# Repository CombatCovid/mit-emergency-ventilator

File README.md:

# MIT Emergency Ventilator (E-Vent) Project Version 3

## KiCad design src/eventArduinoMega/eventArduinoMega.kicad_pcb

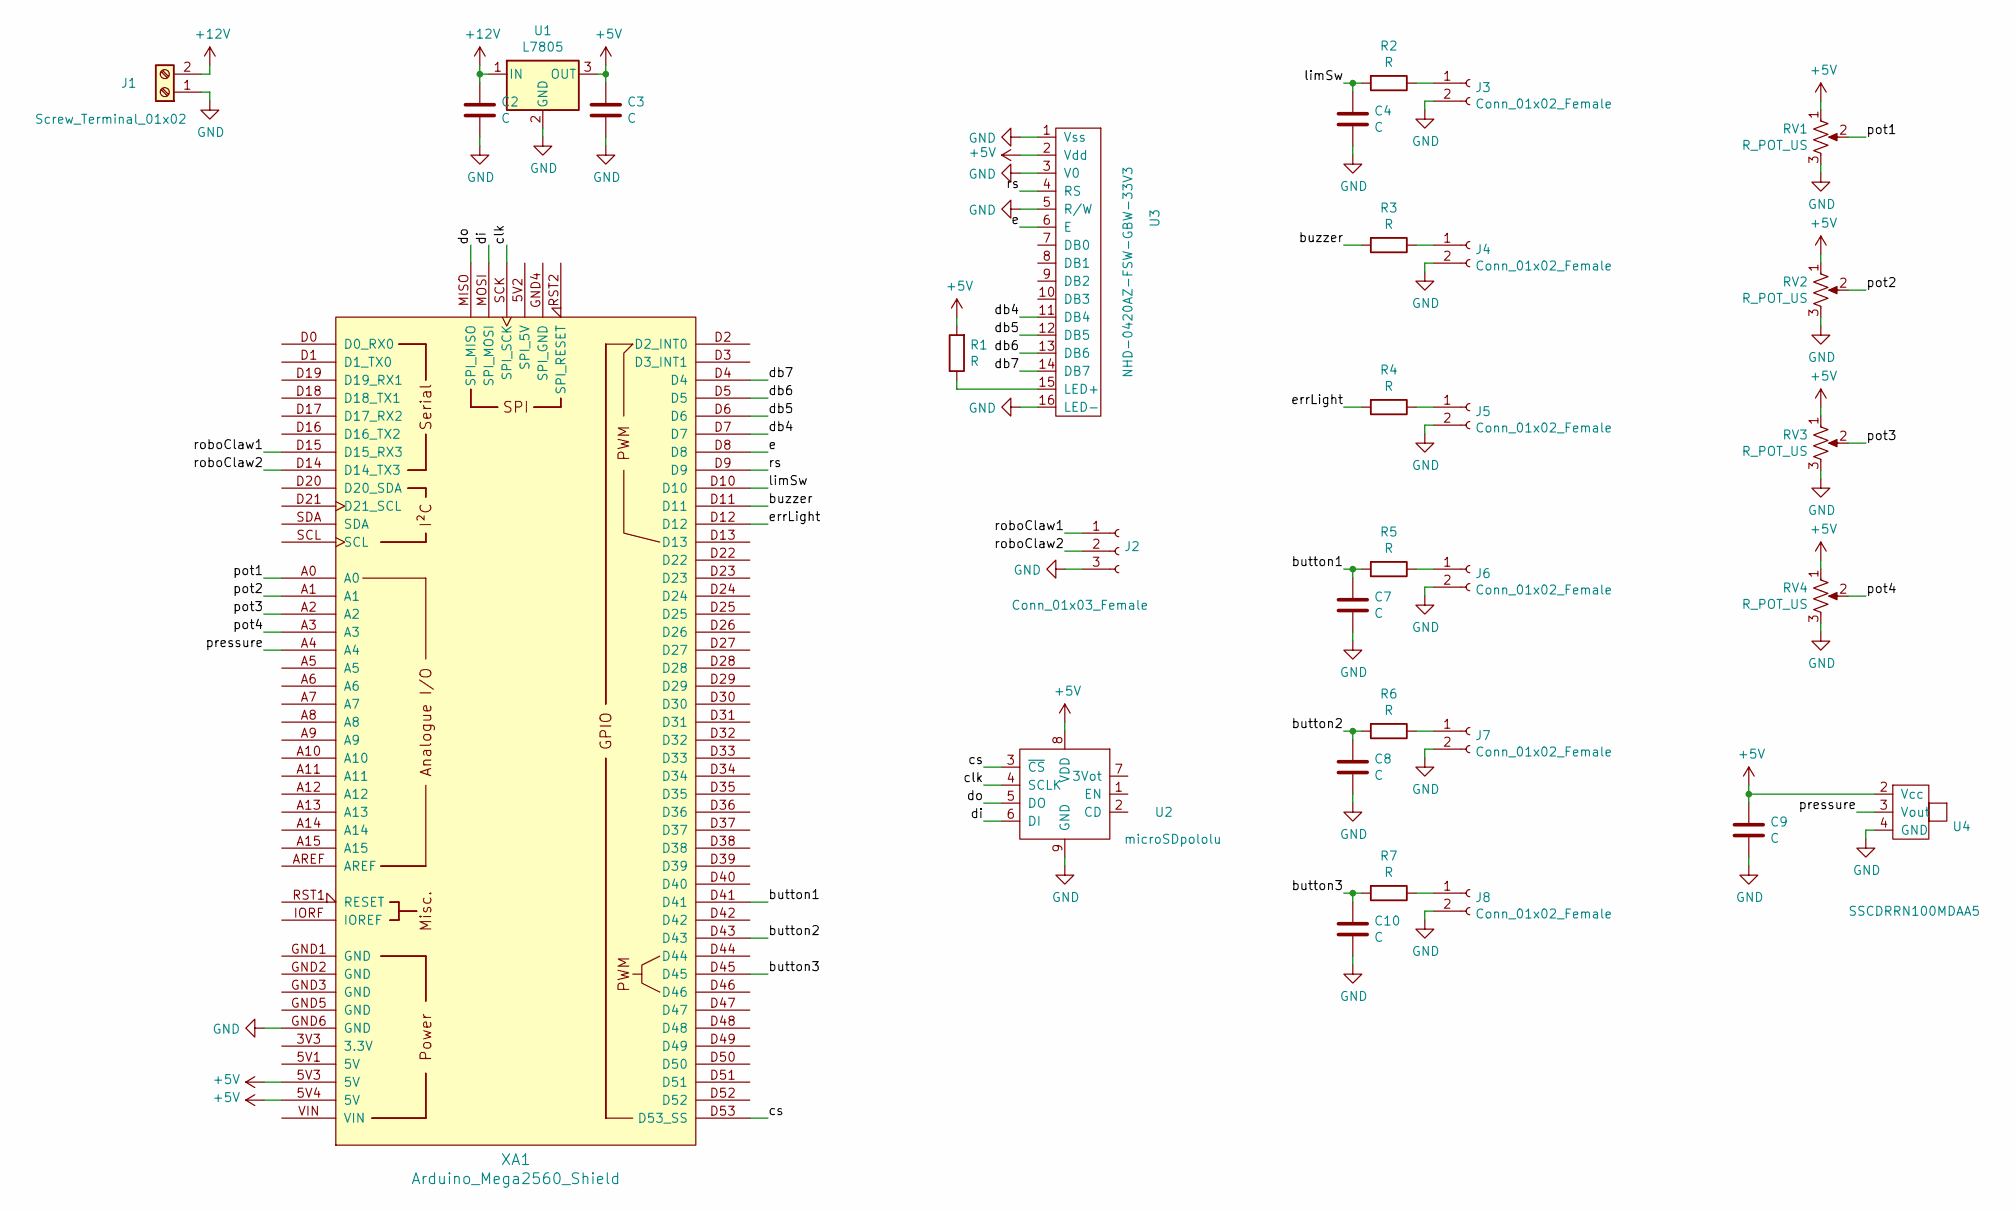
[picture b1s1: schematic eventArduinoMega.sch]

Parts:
C2, C3, C4, C7, C8, C9, C10: C; C_Rect_L7.2mm_W2.5mm_P5.00mm_FKS2_FKP2_MKS2_MKP2
J1: Screw_Terminal_01x02; TerminalBlock_bornier-2_P5.08mm
J2: Conn_01x03_Female; PinHeader_1x03_P2.54mm_Vertical
J3, J4, J5, J6, J7, J8: Conn_01x02_Female; PinHeader_1x02_P2.54mm_Vertical
R1, R2, R3, R4, R5, R6, R7: R; R_Axial_DIN0309_L9.0mm_D3.2mm_P12.70mm_Horizontal
RV1, RV2, RV3, RV4: R_POT_US; pot_panel_surface
U1: L7805; TO-220-3_Widened_Vertical
U2: microSDpololu; microSDpololuBoard
U3: NHD-0420AZ-FSW-GBW-33V3; lcd_4x20_screen_horizontal
U4: SSCDRRN100MDAA5; 100MDA5_pressure_sensor
XA1: Arduino_Mega2560_Shield

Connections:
+5V: C3.1, C9.1, R1.2, RV1.1, RV2.1, RV3.1, RV4.1, U1.3 (OUT), U2.8 (VDD), U3.2 (Vdd), U4.2 (Vcc), XA1.5V3 (5V), XA1.5V4 (5V)
+12V: C2.1, J1.2, U1.1 (IN)
/button1: C7.1, R5.2, XA1.D41
/button2: C8.1, R6.2, XA1.D43
/button3: C10.1, R7.2, XA1.D45
/buzzer: R3.2, XA1.D11; also elsewhere on the board
/clk: U2.4 (SCLK), XA1.SCK (SPI_SCK)
/cs: U2.3 (~CS), XA1.D53 (D53_SS)
/db4: U3.11 (DB4), XA1.D7
/db5: U3.12 (DB5), XA1.D6
/db6: U3.13 (DB6), XA1.D5
/db7: U3.14 (DB7), XA1.D4
/di: U2.6 (DI), XA1.MOSI (SPI_MOSI)
/do: U2.5 (DO), XA1.MISO (SPI_MISO)
/e: U3.6 (E), XA1.D8
/errLight: R4.2, XA1.D12; also elsewhere on the board
/limSw: C4.1, R2.2, XA1.D10
/pot1: RV1.2, XA1.A0
/pot2: RV2.2, XA1.A1
/pot3: RV3.2, XA1.A2
/pot4: RV4.2, XA1.A3
/pressure: U4.3 (Vout), XA1.A4
/roboClaw1: J2.1, XA1.D15 (D15_RX3)
/roboClaw2: J2.2, XA1.D14 (D14_TX3)
/rs: U3.4 (RS), XA1.D9
GND: C2.2, C3.2, C4.2, C7.2, C8.2, C9.2, C10.2, J1.1, J2.3, J3.2, J4.2, J5.2, J6.2, J7.2, J8.2, RV1.3, RV2.3, RV3.3, RV4.3, U1.2 (GND), U2.9 (GND), U3.1 (Vss), U3.3 (V0), U3.5 (R/W), U3.16 (LED-), U4.4 (GND), XA1.GND6 (GND); also elsewhere on the board
unnamed: J3.1, R2.1
unnamed: J4.1, R3.1
unnamed: J5.1, R4.1
unnamed: J6.1, R5.1
unnamed: J7.1, R6.1
unnamed: J8.1, R7.1
unnamed: R1.1, U3.15 (LED+)

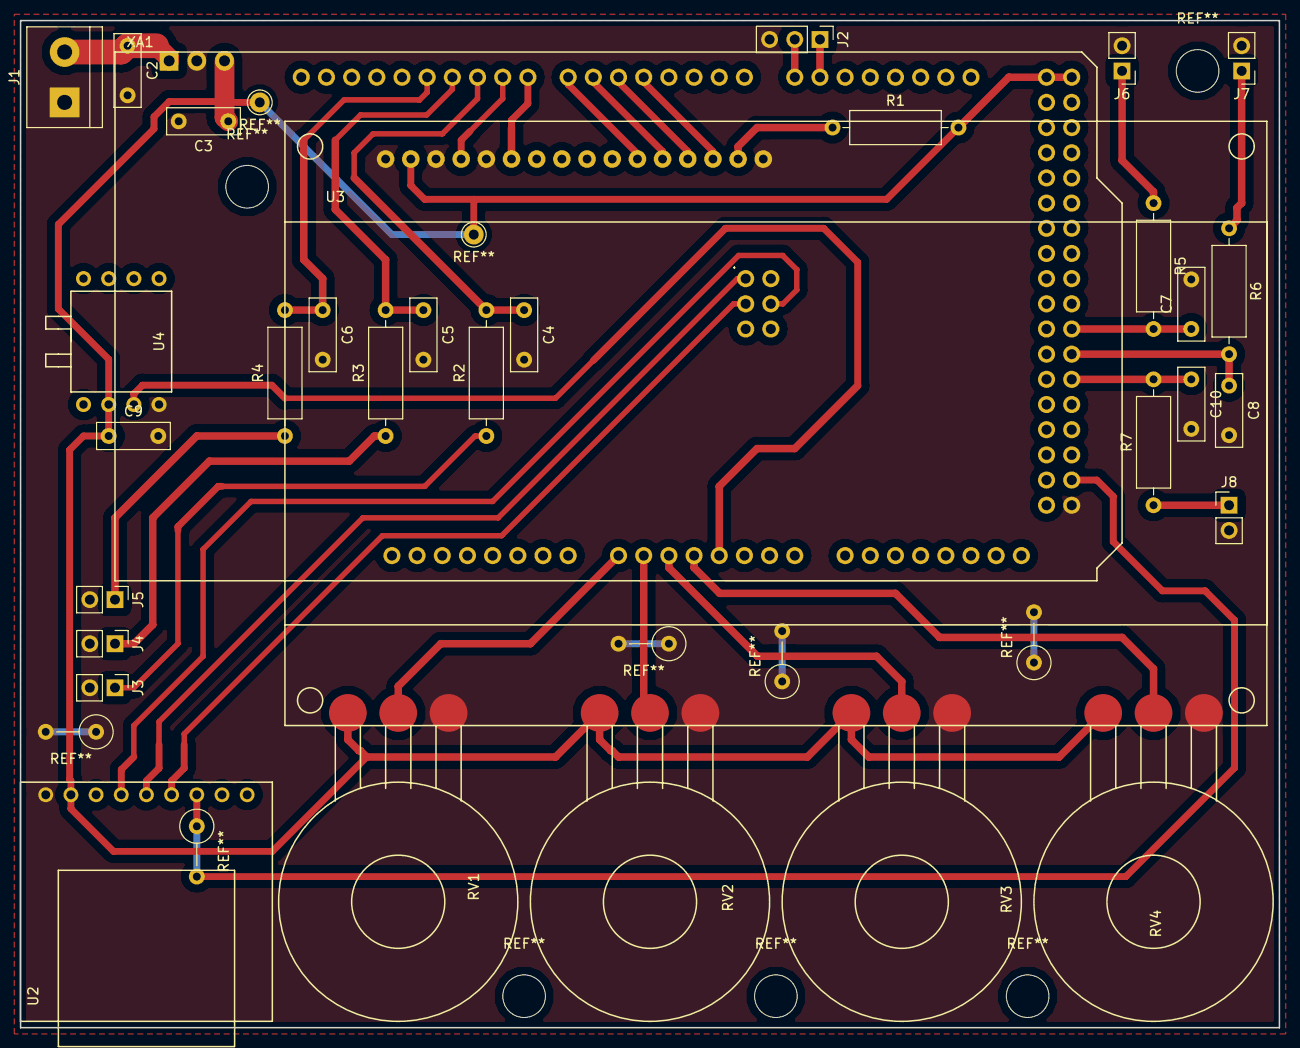
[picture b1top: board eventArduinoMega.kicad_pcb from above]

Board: 2 copper layers, 127.0 x 101.6 mm, 33 parts (1 on the bottom side), 33 nets.

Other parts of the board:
C5, C6: C; C_Rect_L7.2mm_W2.5mm_P5.00mm_FKS2_FKP2_MKS2_MKP2

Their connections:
/buzzer: C5.1; also elsewhere on the board
/errLight: C6.1; also elsewhere on the board
GND: C5.2, C6.2; also elsewhere on the board

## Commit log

2020-03-28 documentation-e-vent from MIT
2020-03-28 img inside docs
2020-03-28 EN-folder-complete
2020-03-28 complete -pdf-EN folder
2020-03-28 picture-correction-in-testing-results
2020-03-28 ES-folder-complete
2020-03-28 relocating dxf files
2020-03-28 changing the path for dxf files
2020-03-28 changing url
2020-03-28 copying images inside the docs folder
2020-03-31 Updated metadata
2020-04-03 removed unecessary images
2020-04-03 Update to our spec for each repo's summary info, which the app will present
2020-04-04 Also updated with front-matter items learned from other repos...
2020-04-05 normalize the image path as should be -- in the docs folder. Correct a spelling noticed in one of the docs
2020-04-06 Similar to just now on medical-shields-for-3d-printing, correct local C:\ pc file links to ../somewhere etc. proper universal links that work on the web and app. Also some minor issues caught and fix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
2020-04-06 tiny fix on fixes...
2020-04-06 found one more misformed link -- spaces in it...
2020-04-08 deleted img folder
2020-04-09 Provide repo top-level metadata that will be used for the Combat Covid project, capable in multiple languages. The data is arranged primarily a separate metadata.yaml which is likely to be easiest fo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
2020-04-09 Let's try the longest name that looks possible for the MIT Ventilator -- and alter the Yaml tag for it to make clear it's the shortName to used by the primary Finder-Viewer app software.
2020-04-10 added instructions per trailing --- marker: never have it in metadata.yaml, and why...
2020-04-13 Update to the standard for the project being produced by Jose and Clive. This same file will go into the doc-template repo, for use as a model.
2020-04-16 This is a first working model, to prove out our simplified design for per-language metadata. There are also key additions in this upgrade, three new fields of definite importance, and always having b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
    A side note is that this is being pushed to the _master_ branch, and the moment will soon end for doing that, as constructing content will move to the very familiar and effective way that most pr
2020-04-17 updated metadata files
2020-05-03 metadata-version3
2020-05-03 adding metadata version1 and 2
2020-05-03 removing file
2020-05-03 update metadata
2020-05-03 restructuring files
2020-05-03 update docs
2020-05-03 bom complete and clinical studies
2020-05-03 complete documentation in EN
2020-05-03 adding images to img outside version_3 folder
2020-07-14 Add a finderPriority for ordering
2020-07-14 finderPriorities to gaps of 100, so they can be adjusted individually
